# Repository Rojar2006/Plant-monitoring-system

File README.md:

------------PLANT MONITORING SYSTEM--------------

A smart plant monitoring system using the esp32-WROOM-C3 module, and custom designed PCB.

UNIQUENESS OF THE PROJECT
  -Unlike most DIY projects which use the development board, this uses the raw esp32  microcontroller with a custom PCB.

  ------KEY FEATURES------
    - ESP32-WROOM-C3 module with wifi and bluetooth connectivity.
    - Fully custom PCB designed from scratch.
    - Soil moisture sensor, temperature and humidity sensor, and light intensity sensor integrated into the PCB.
    - Uses capacitors for entering the bootloader mode, instead of using manual buttons.
    - micro-USB for programming the microcontroller, with a USB-UART master bridge.
    - Integrated voltage regulator for the optimal 3.3V supply for the esp32.
    - Barrel-jack for external power, with Schottky diode to prevent backfeeding when multiple power sources are present.
    - Optioinal cloud connectivity.
    - Designed for low-cost scalable deployment.

-----------HARDWARE OVERVIEW-------------
    - ESP32-WROOM-C3 bare module
    - AMS1117 3.3V regulator (or similar LDO)
    - USB-to-Serial (CH340 / CP2102) for flashing/debug
    - Soil Moisture Sensor
    - DHT11 or DHT22 Sensor
    - Relay Module (optically isolated)
    - Decoupling capacitors, pull-up resistors.
-----------PCB DESIGN--------------
    - Designed in KiCAD
    - custom Copper route, antenna clearance.
    - Proper boot configuration circuitry.
    - USB and power input protection.

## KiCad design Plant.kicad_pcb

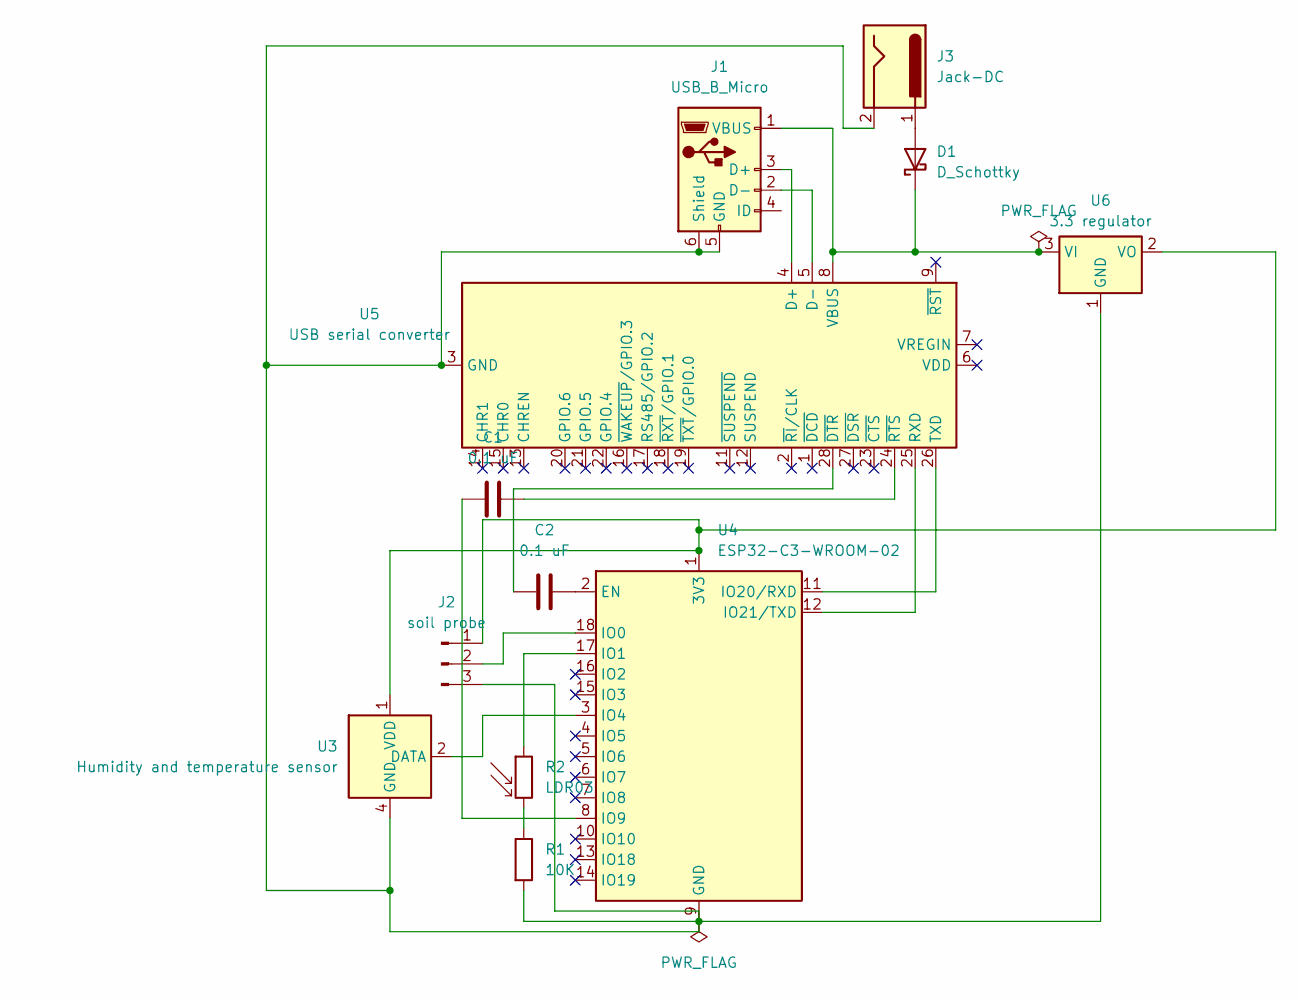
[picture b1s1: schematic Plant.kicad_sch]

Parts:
C1, C2: 0.1 uF; C_Disc_D3.0mm_W1.6mm_P2.50mm
D1: D_Schottky; D_SMA
J1: USB_B_Micro; USB_Micro-B_Molex-105017-0001
J2: soil probe; PinHeader_1x03_P1.00mm_Horizontal
J3: Jack-DC; BarrelJack_GCT_DCJ200-10-A_Horizontal
R1: 10K; R_0201_0603Metric
R2: LDR03; R_LDR_10x8.5mm_P7.6mm_Vertical
U3: Humidity and temperature sensor; Aosong_DHT11_5.5x12.0_P2.54mm
U4: ESP32-C3-WROOM-02
U5: USB serial converter; QFN-28-1EP_5x5mm_P0.5mm_EP3.35x3.35mm
U6: 3.3 regulator; SOT-223-3_TabPin2

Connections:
unnamed: D1.2 (A), J3.1
unnamed: D1.1 (K), J1.1 (VBUS), U5.8 (VBUS), U6.3 (VI)
unnamed: J1.3 (D+), U5.4 (D+)
unnamed: J1.2 (D-), U5.5 (D-)
unnamed: J1.5 (GND), J1.6 (Shield), J2.3, J3.2, R1.2, U3.4 (GND), U4.9 (GND), U4.19 (GND), U5.3 (GND), U5.29 (GND), U6.1 (GND)
unnamed: J2.1, U3.1 (VDD), U4.1 (3V3), U6.2 (VO)
unnamed: J2.2, U4.18 (IO0)
unnamed: R1.1, R2.2
unnamed: U3.2 (DATA), U4.3 (IO4)
unnamed: C2.2, U4.2 (EN)
unnamed: R2.1, U4.17 (IO1)
unnamed: C1.1, U4.8 (IO9)
unnamed: U4.11 (IO20/RXD), U5.26 (TXD)
unnamed: U4.12 (IO21/TXD), U5.25 (RXD)
unnamed: C2.1, U5.28 (~DTR)
unnamed: C1.2, U5.24 (~RTS)

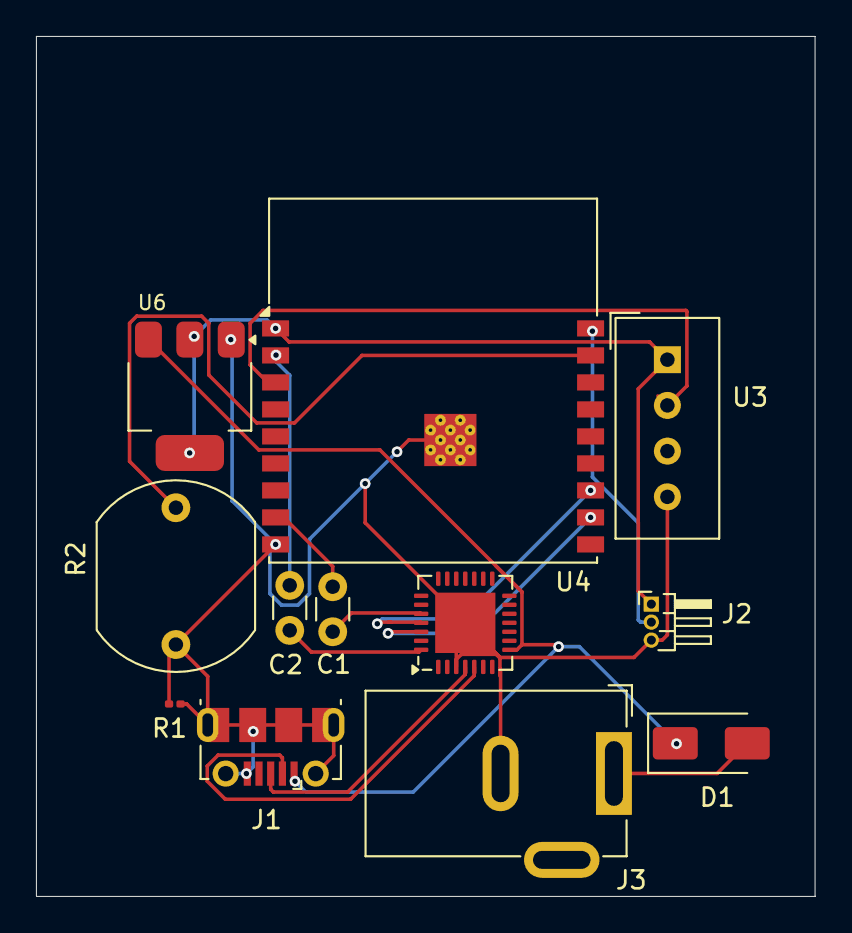
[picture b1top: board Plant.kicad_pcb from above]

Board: 2 copper layers, 43.3 x 47.8 mm, 12 parts (0 on the bottom side), 16 nets.

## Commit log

2025-07-19 updated readme file
